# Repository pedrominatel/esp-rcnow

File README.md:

# esp-rcnow
ESP-IDF project for remote control based on the ESP-NOW protocol.

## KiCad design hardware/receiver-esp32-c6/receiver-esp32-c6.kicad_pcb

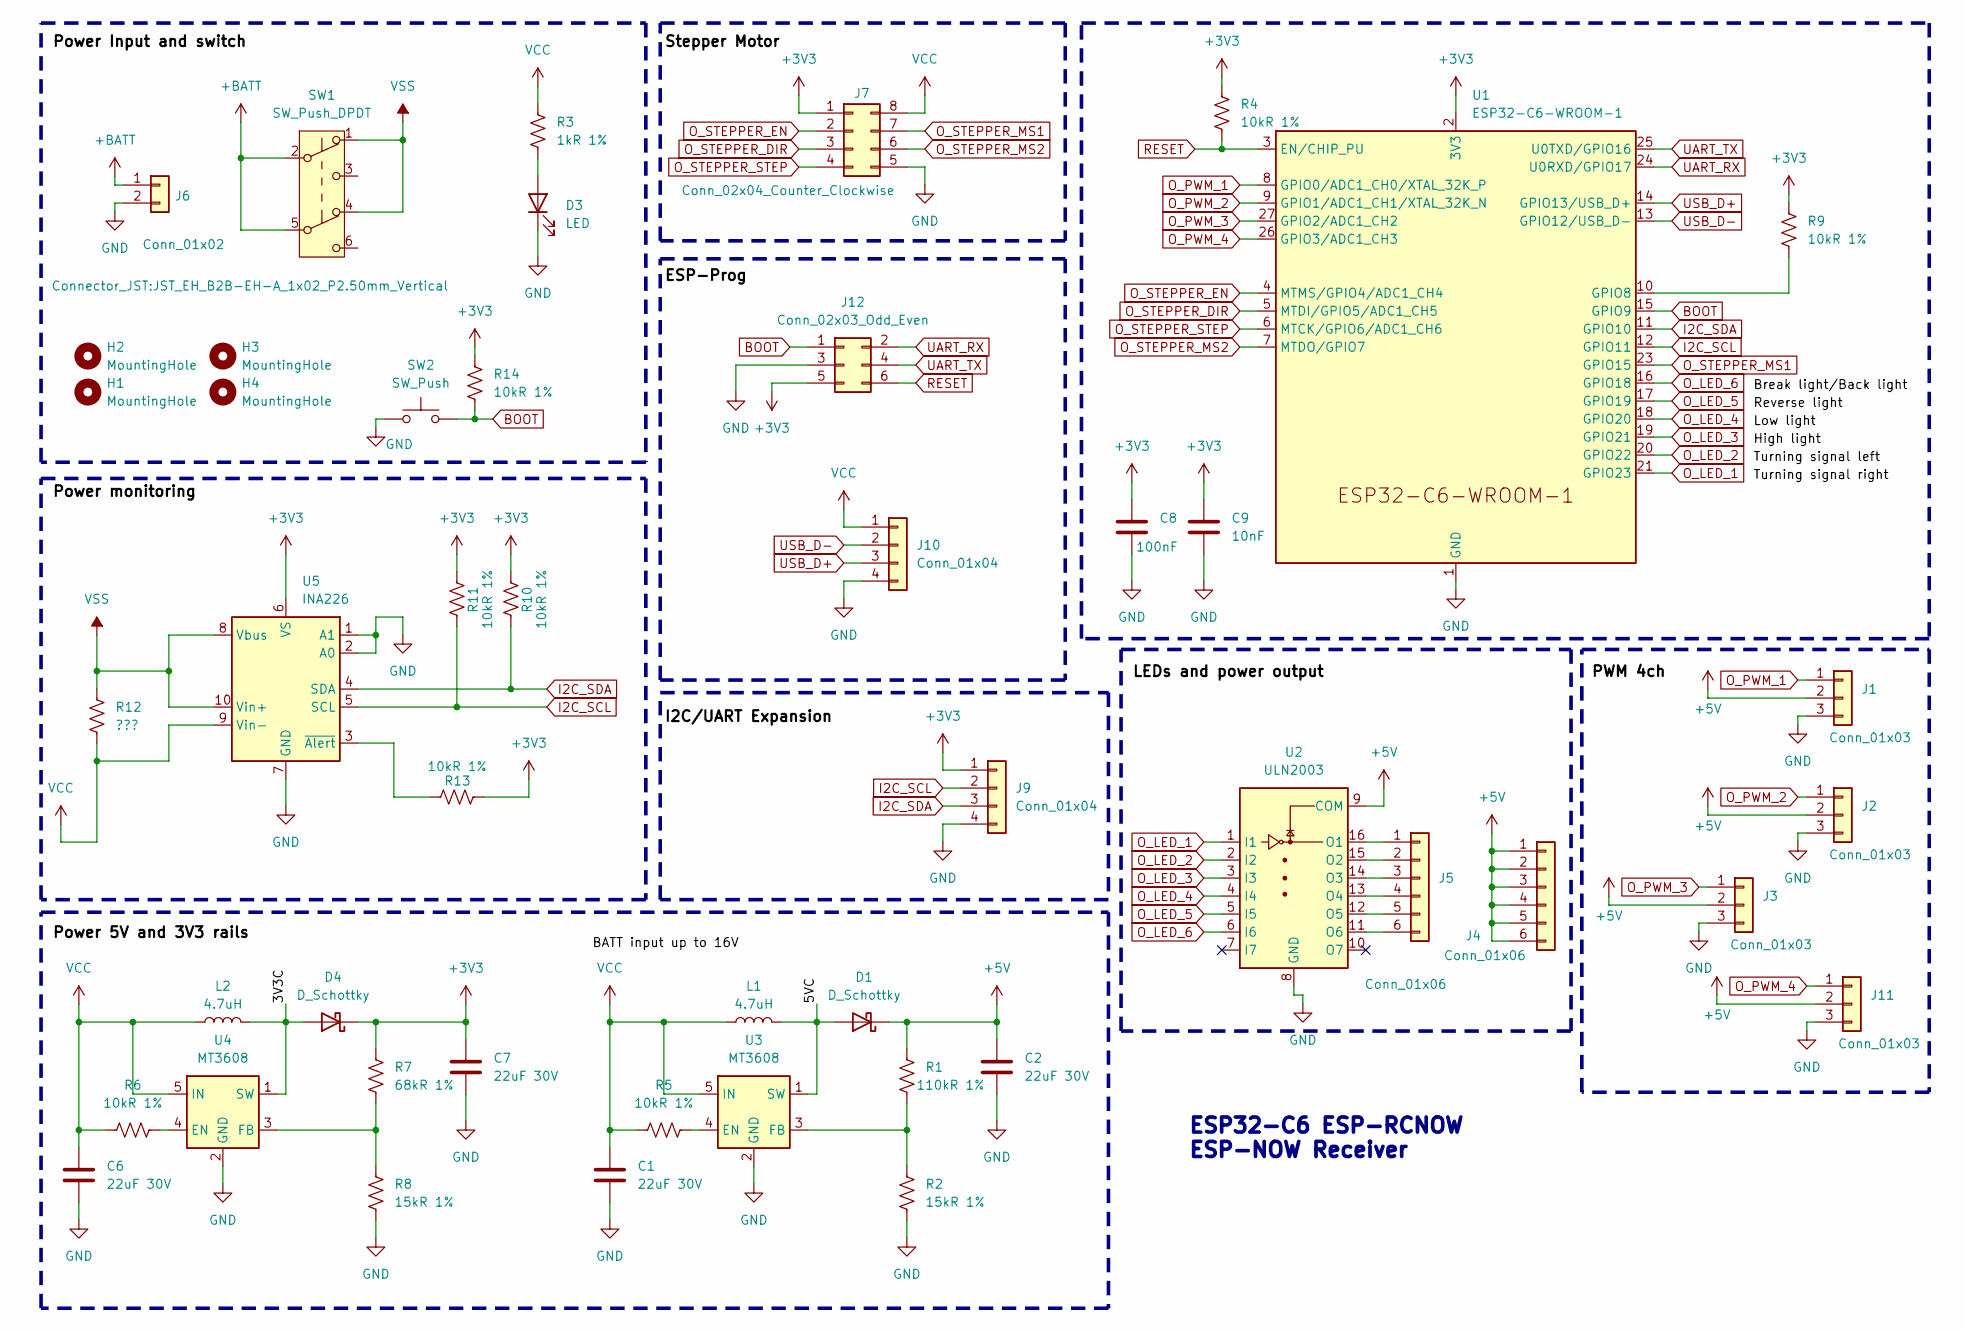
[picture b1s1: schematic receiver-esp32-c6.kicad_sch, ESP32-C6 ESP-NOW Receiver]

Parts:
C1, C2, C6, C7: 22uF 30V; C_0603_1608Metric
C8: 100nF; C_0603_1608Metric
C9: 10nF; C_0603_1608Metric
D1, D4: D_Schottky; D_SMF
D3: LED; LED_0603_1608Metric
H1, H2, H3, H4: MountingHole; MountingHole_4mm_Pad_TopBottom
J1, J2, J3, J11: Conn_01x03; PinHeader_1x03_P2.54mm_Vertical
J4, J5: Conn_01x06; PinHeader_1x06_P2.54mm_Vertical
J6: Conn_01x02; JST_EH_B2B-EH-A_1x02_P2.50mm_Vertical
J7: Conn_02x04_Counter_Clockwise; IDC-Header_2x04_P2.54mm_Vertical
J9, J10: Conn_01x04; PinHeader_1x04_P2.54mm_Vertical
J12: Conn_02x03_Odd_Even; PinHeader_2x03_P1.27mm_Vertical_SMD
L1, L2: 4.7uH; L_Changjiang_FNR5020S
R1: 110kR 1%; R_0603_1608Metric
R2, R8: 15kR 1%; R_0603_1608Metric
R3: 1kR 1%; R_0603_1608Metric
R4, R5, R6, R9, R10, R11, R13, R14: 10kR 1%; R_0603_1608Metric
R7: 68kR 1%; R_0603_1608Metric
R12: ???; R_0805_2012Metric
SW1: SW_Push_DPDT; Switch-6P-2way
SW2: SW_Push; SW_SPST_PTS647_Sx38
U1: ESP32-C6-WROOM-1
U2: ULN2003; SOP-16_3.9x9.9mm_P1.27mm
U3, U4: MT3608; SOT-23-6
U5: INA226; VSSOP-10_3x3mm_P0.5mm

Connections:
+3V3: C7.1, C8.1, C9.1, D4.1 (K), J7.1, J9.1, J12.5, R4.1, R7.1, R9.1, R10.2, R11.2, R13.1, R14.1, U1.2 (3V3), U5.6 (VS)
+5V: C2.1, D1.1 (K), J1.2, J2.2, J3.2, J4.1, J4.2, J4.3, J4.4, J4.5, J4.6, J11.2, R1.1, U2.9 (COM)
+BATT: J6.1, SW1.2 (B), SW1.5 (B)
/3V3C: D4.2 (A), L2.2, U4.1 (SW)
/5VC: D1.2 (A), L1.2, U3.1 (SW)
BOOT: J12.1, R14.2, SW2.2, U1.15 (GPIO9)
GND: C1.2, C2.2, C6.2, C7.2, C8.2, C9.2, D3.1 (K), J1.3, J2.3, J3.3, J6.2, J7.5, J9.4, J10.4, J11.3, J12.3, R2.2, R8.2, SW2.1, U1.1 (GND), U1.28 (GND), U1.29 (GND), U2.8 (GND), U3.2 (GND), U4.2 (GND), U5.1 (A1), U5.2 (A0), U5.7 (GND)
I2C_SCL: J9.2, R11.1, U1.12 (GPIO11), U5.5 (SCL)
I2C_SDA: J9.3, R10.1, U1.11 (GPIO10), U5.4 (SDA)
unnamed: D3.2 (A), R3.2
unnamed: J5.1, U2.16 (O1)
unnamed: J5.2, U2.15 (O2)
unnamed: J5.3, U2.14 (O3)
unnamed: J5.4, U2.13 (O4)
unnamed: J5.5, U2.12 (O5)
unnamed: J5.6, U2.11 (O6)
unnamed: R9.2, U1.10 (GPIO8)
unnamed: R5.2, U3.4 (EN)
unnamed: R1.2, R2.1, U3.3 (FB)
unnamed: R6.2, U4.4 (EN)
unnamed: R7.2, R8.1, U4.3 (FB)
unnamed: R13.2, U5.3 (~Alert)
O_LED_1: U1.21 (GPIO23), U2.1 (I1)
O_LED_2: U1.20 (GPIO22), U2.2 (I2)
O_LED_3: U1.19 (GPIO21), U2.3 (I3)
O_LED_4: U1.18 (GPIO20), U2.4 (I4)
O_LED_5: U1.17 (GPIO19), U2.5 (I5)
O_LED_6: U1.16 (GPIO18), U2.6 (I6)
O_PWM_1: J1.1, U1.8 (GPIO0/ADC1_CH0/XTAL_32K_P)
O_PWM_2: J2.1, U1.9 (GPIO1/ADC1_CH1/XTAL_32K_N)
O_PWM_3: J3.1, U1.27 (GPIO2/ADC1_CH2)
O_PWM_4: J11.1, U1.26 (GPIO3/ADC1_CH3)
O_STEPPER_DIR: J7.3, U1.5 (MTDI/GPIO5/ADC1_CH5)
O_STEPPER_EN: J7.2, U1.4 (MTMS/GPIO4/ADC1_CH4)
O_STEPPER_MS1: J7.7, U1.23 (GPIO15)
O_STEPPER_MS2: J7.6, U1.7 (MTDO/GPIO7)
O_STEPPER_STEP: J7.4, U1.6 (MTCK/GPIO6/ADC1_CH6)
RESET: J12.6, R4.2, U1.3 (EN/CHIP_PU)
UART_RX: J12.2, U1.24 (U0RXD/GPIO17)
UART_TX: J12.4, U1.25 (U0TXD/GPIO16)
USB_D+: J10.3, U1.14 (GPIO13/USB_D+)
USB_D-: J10.2, U1.13 (GPIO12/USB_D-)
VCC: C1.1, C6.1, J7.8, J10.1, L1.1, L2.1, R3.1, R5.1, R6.1, R12.2, U3.5 (IN), U4.5 (IN), U5.9 (Vin-)
VSS: R12.1, SW1.1 (A), SW1.4 (A), U5.8 (Vbus), U5.10 (Vin+)

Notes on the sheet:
ESP32-C6 ESP-RCNOW ESP-NOW Receiver

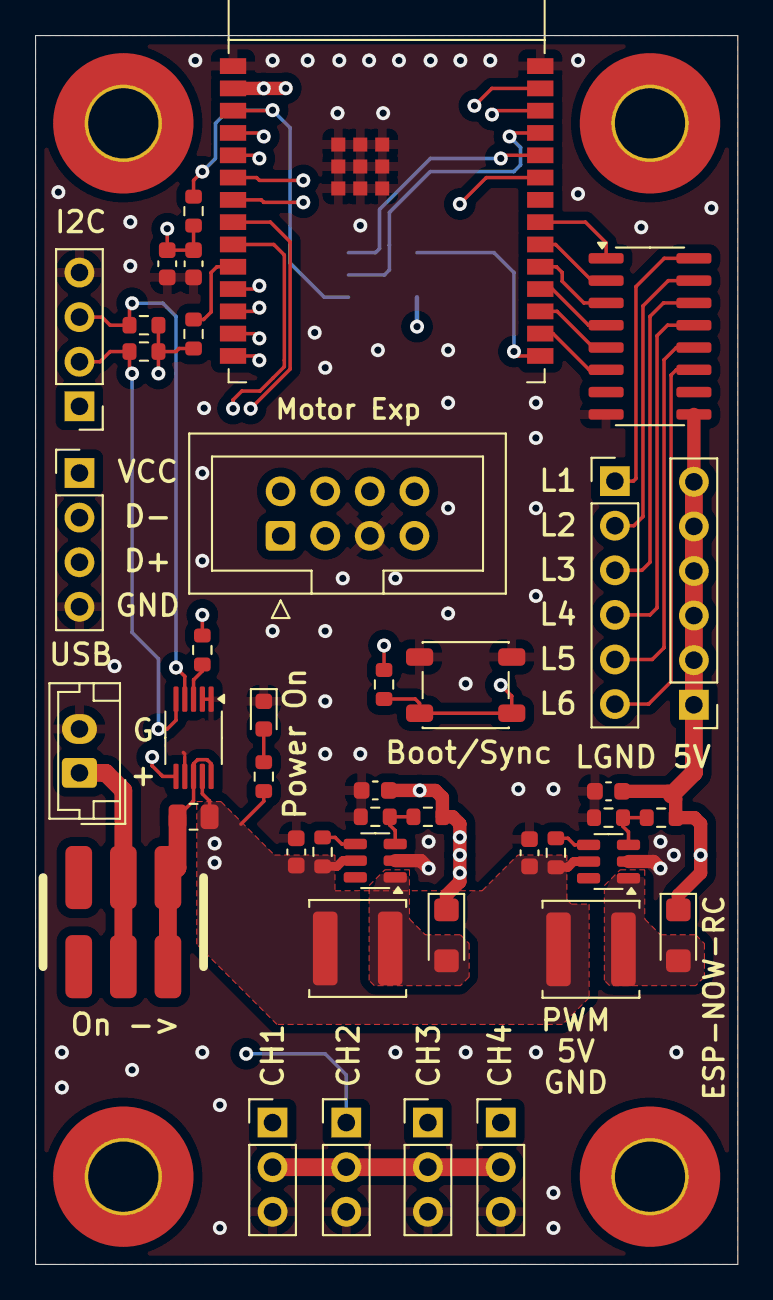
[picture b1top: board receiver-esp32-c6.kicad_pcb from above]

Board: 4 copper layers, 40.0 x 70.0 mm, 47 parts (1 on the bottom side), 44 nets.

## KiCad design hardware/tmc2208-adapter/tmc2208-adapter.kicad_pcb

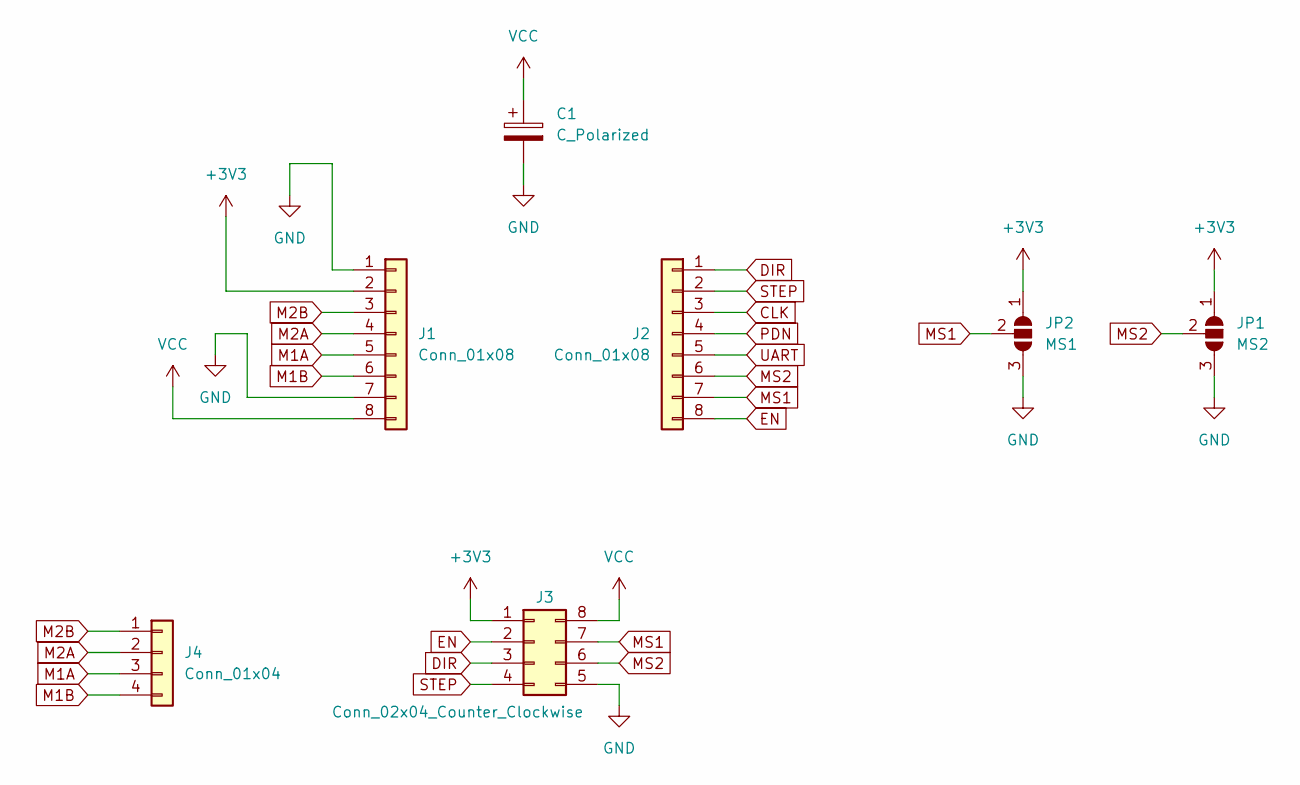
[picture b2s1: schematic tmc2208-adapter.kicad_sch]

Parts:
C1: C_Polarized; CP_Radial_D13.0mm_P7.50mm
J1, J2: Conn_01x08; PinSocket_1x08_P2.54mm_Vertical
J3: Conn_02x04_Counter_Clockwise; IDC-Header_2x04_P2.54mm_Vertical
J4: Conn_01x04; JST_EH_B4B-EH-A_1x04_P2.50mm_Vertical
JP1: MS2; SolderJumper-3_P1.3mm_Open_Pad1.0x1.5mm
JP2: MS1; SolderJumper-3_P1.3mm_Open_Pad1.0x1.5mm

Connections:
+3V3: J1.2, J3.1, JP1.1 (A), JP2.1 (A)
CLK: J2.3
DIR: J2.1, J3.3
EN: J2.8, J3.2
GND: C1.2, J1.1, J1.7, J3.5, JP1.3 (B), JP2.3 (B)
M1A: J1.5, J4.3
M1B: J1.6, J4.4
M2A: J1.4, J4.2
M2B: J1.3, J4.1
MS1: J2.7, J3.7, JP2.2 (C)
MS2: J2.6, J3.6, JP1.2 (C)
PDN: J2.4
STEP: J2.2, J3.4
UART: J2.5
VCC: C1.1, J1.8, J3.8

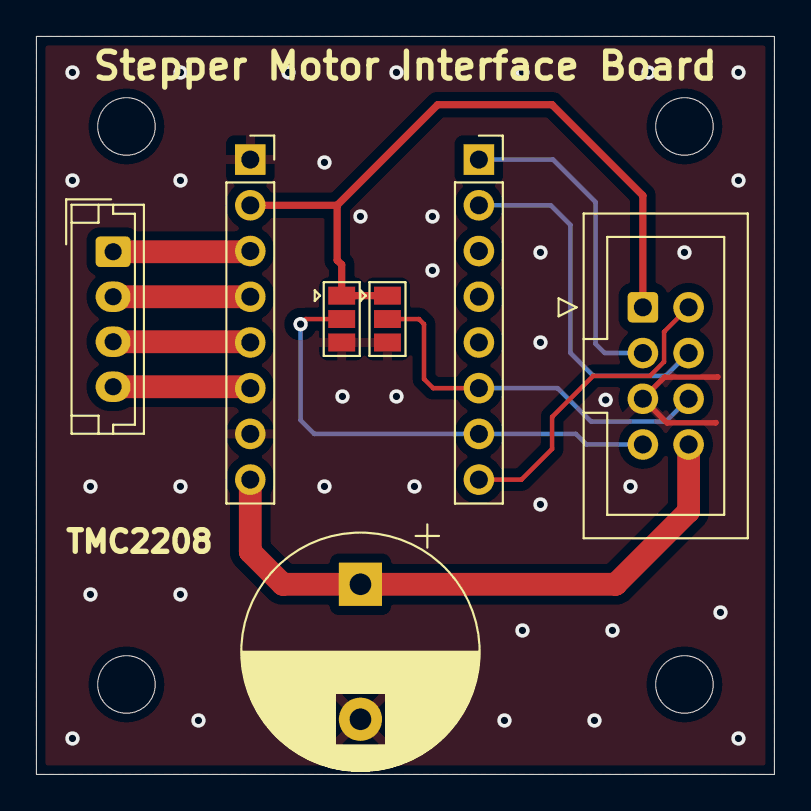
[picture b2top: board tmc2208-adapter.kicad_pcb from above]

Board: 2 copper layers, 41.0 x 41.0 mm, 7 parts (0 on the bottom side), 12 nets.

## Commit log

2025-01-11 Project skeleton
2025-01-11 Components skeleton
2025-01-13 Added dependencies and esp-now init
2025-02-08 WIP and added some features
2025-02-08 WIP and gitignore update
2025-04-18 First production version - with issues
2025-04-18 Fixed the ESP-PROG pinout
2025-04-18 Removed local configuration file
2026-01-30 Initial plan
2026-01-30 Fix code quality issues: typo, unused variable, and missing error check
2026-01-30 Add error checking for esp_event_loop_create_default()
2026-01-30 Remove CodeQL artifact and update .gitignore
2026-01-30 Add comment explaining error handling pattern choice
